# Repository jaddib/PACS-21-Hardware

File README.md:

# PACS-21-Hardware
Here is where we will store our schematics and PCBs
:)

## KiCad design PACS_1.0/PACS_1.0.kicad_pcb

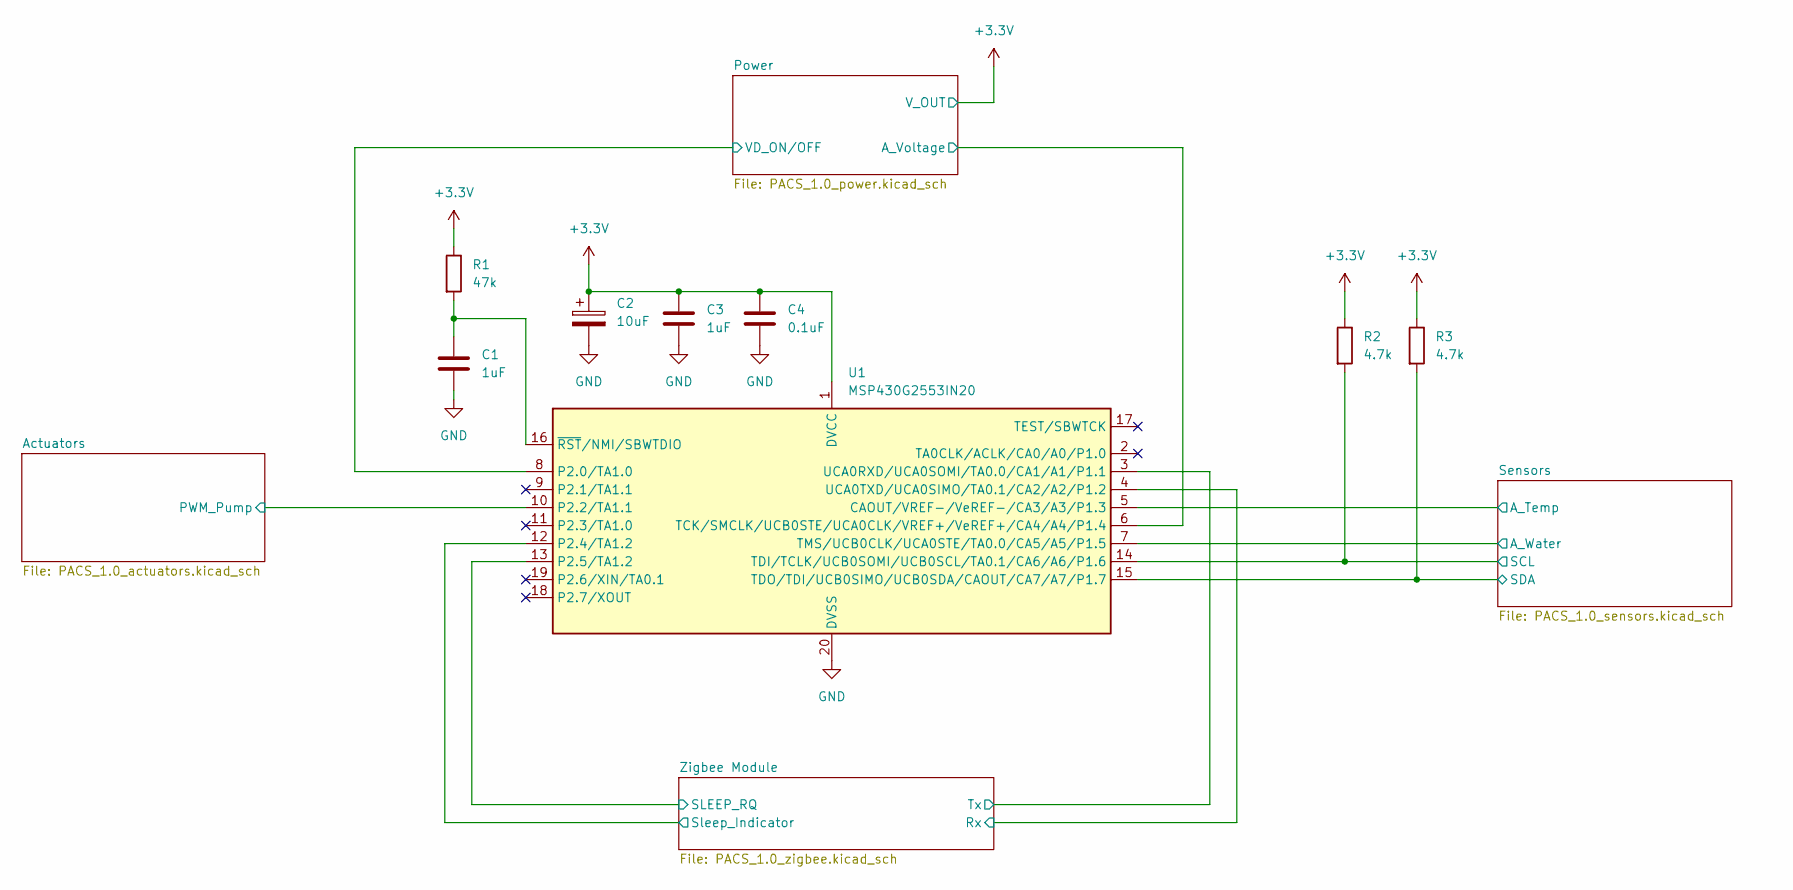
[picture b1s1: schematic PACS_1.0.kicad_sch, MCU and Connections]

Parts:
C1, C3: 1uF; C_0603_1608Metric
C2: 10uF; C_0805_2012Metric
C4: 0.1uF; C_0402_1005Metric
R1: 47k; R_0603_1608Metric
R2, R3: 4.7k; R_0402_1005Metric
U1: MSP430G2553IN20; DIP-20_W7.62mm

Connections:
+3.3V: C2.1, C3.1, C4.1, R1.1, R2.1, R3.1, U1.1 (DVCC); also elsewhere on the board
/Actuators/PWM_Pump: U1.10 (P2.2/TA1.1); also elsewhere on the board
/Power/A_Voltage: U1.6 (TCK/SMCLK/UCB0STE/UCA0CLK/VREF+/VeREF+/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); also elsewhere on the board
/Power/VD_ON/OFF: U1.8 (P2.0/TA1.0); also elsewhere on the board
/Sensors/A_Temp: U1.5 (CAOUT/VREF-/VeREF-/CA3/A3/P1.3); also elsewhere on the board
/Sensors/A_Water: U1.7 (TMS/UCB0CLK/UCA0STE/TA0.0/CA5/A5/P1.5); also elsewhere on the board
/Sensors/SCL: R2.2, U1.14 (TDI/TCLK/UCB0SOMI/UCB0SCL/TA0.1/CA6/A6/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); also elsewhere on the board
/Sensors/SDA: R3.2, U1.15 (TDO/TDI/UCB0SIMO/UCB0SDA/CAOUT/CA7/A7/P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); also elsewhere on the board
/Zigbee Module/Rx: U1.4 (UCA0TXD/UCA0SIMO/TA0.1/CA2/A2/P1.2); also elsewhere on the board
/Zigbee Module/SLEEP_RQ: U1.13 (P2.5/TA1.2); also elsewhere on the board
/Zigbee Module/Sleep_Indicator: U1.12 (P2.4/TA1.2); also elsewhere on the board
/Zigbee Module/Tx: U1.3 (UCA0RXD/UCA0SOMI/TA0.0/CA1/A1/P1.1); also elsewhere on the board
GND: C1.2, C2.2, C3.2, C4.2, U1.20 (DVSS); also elsewhere on the board
unnamed: C1.1, R1.2, U1.16 (~RST/NMI/SBWTDIO)

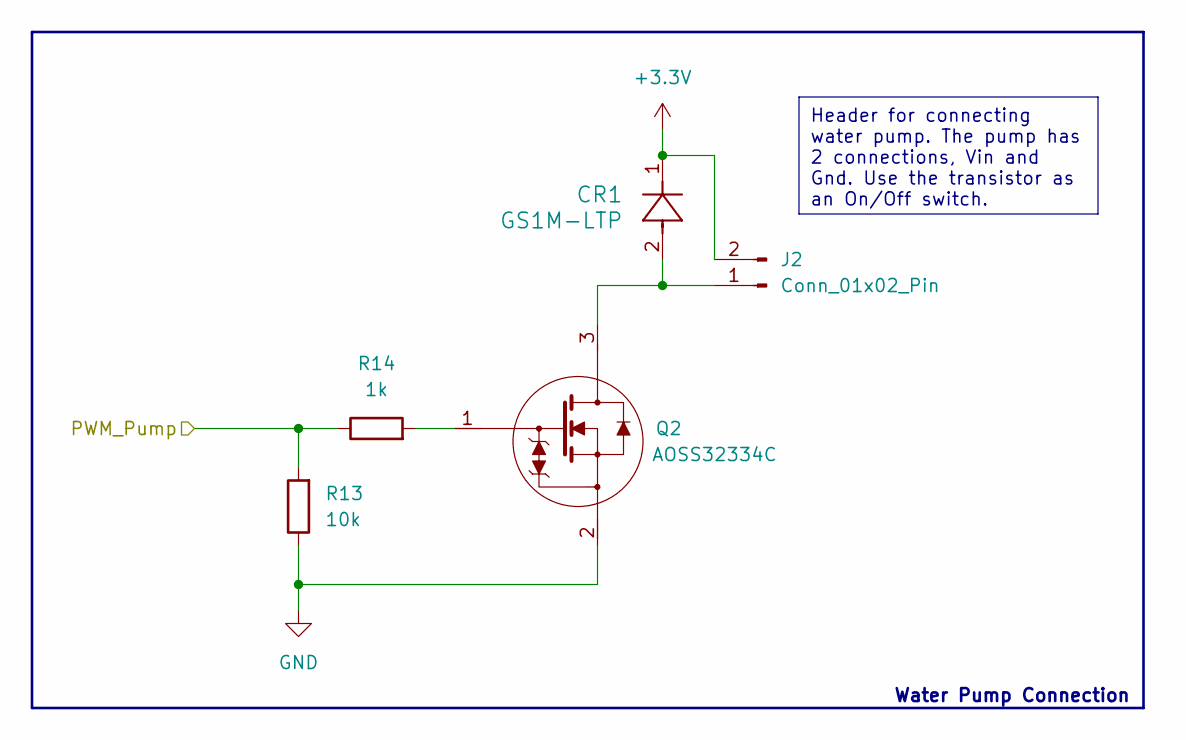
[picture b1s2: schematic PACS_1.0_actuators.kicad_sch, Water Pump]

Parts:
CR1: GS1M-LTP; D_SMA
J2: Conn_01x02_Pin; JST_EH_B2B-EH-A_1x02_P2.50mm_Vertical
Q2: TSOT-23
R13: 10k; R_0402_1005Metric
R14: 1k; R_0402_1005Metric

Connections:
+3.3V: CR1.1, J2.2; also elsewhere on the board
/Actuators/PWM_Pump: R13.2, R14.1; also elsewhere on the board
GND: Q2.2, R13.1; also elsewhere on the board
unnamed: CR1.2, J2.1, Q2.3
unnamed: Q2.1, R14.2

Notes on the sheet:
Header for connecting water pump. The pump has 2 connections, Vin and Gnd. Use the transistor as an On/Off switch.
Water Pump Connection

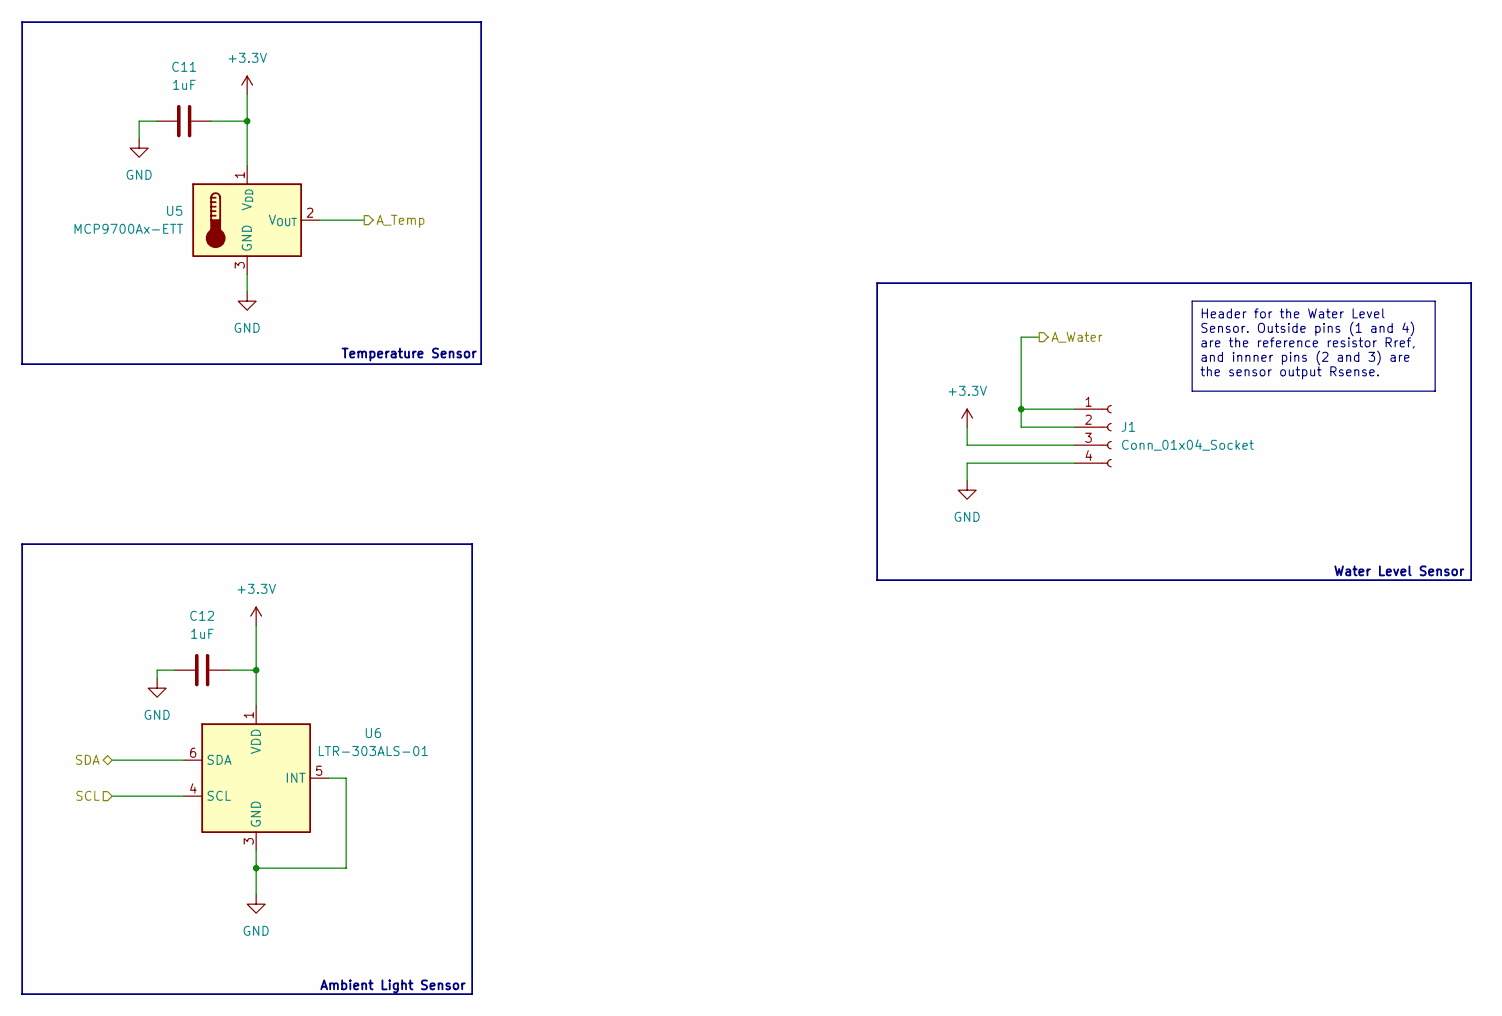
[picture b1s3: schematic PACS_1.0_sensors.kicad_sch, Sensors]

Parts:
C11, C12: 1uF; C_0603_1608Metric
J1: Conn_01x04_Socket; PinSocket_1x04_P2.54mm_Vertical
U5: MCP9700Ax-ETT; SOT-23
U6: LTR-303ALS-01; Lite-On_LTR-303ALS-01

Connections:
+3.3V: C11.2, C12.2, J1.3, U5.1 (V_{DD}), U6.1 (VDD); also elsewhere on the board
/Sensors/A_Temp: U5.2 (V_{OUT}); also elsewhere on the board
/Sensors/A_Water: J1.1, J1.2; also elsewhere on the board
/Sensors/SCL: U6.4 (SCL); also elsewhere on the board
/Sensors/SDA: U6.6 (SDA); also elsewhere on the board
GND: C11.1, C12.1, J1.4, U5.3 (GND), U6.3 (GND), U6.5 (INT); also elsewhere on the board

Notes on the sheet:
Header for the Water Level Sensor. Outside pins (1 and 4) are the reference resistor Rref, and innner pins (2 and 3) are the sensor output Rsense.
Water Level Sensor
Temperature Sensor
Ambient Light Sensor

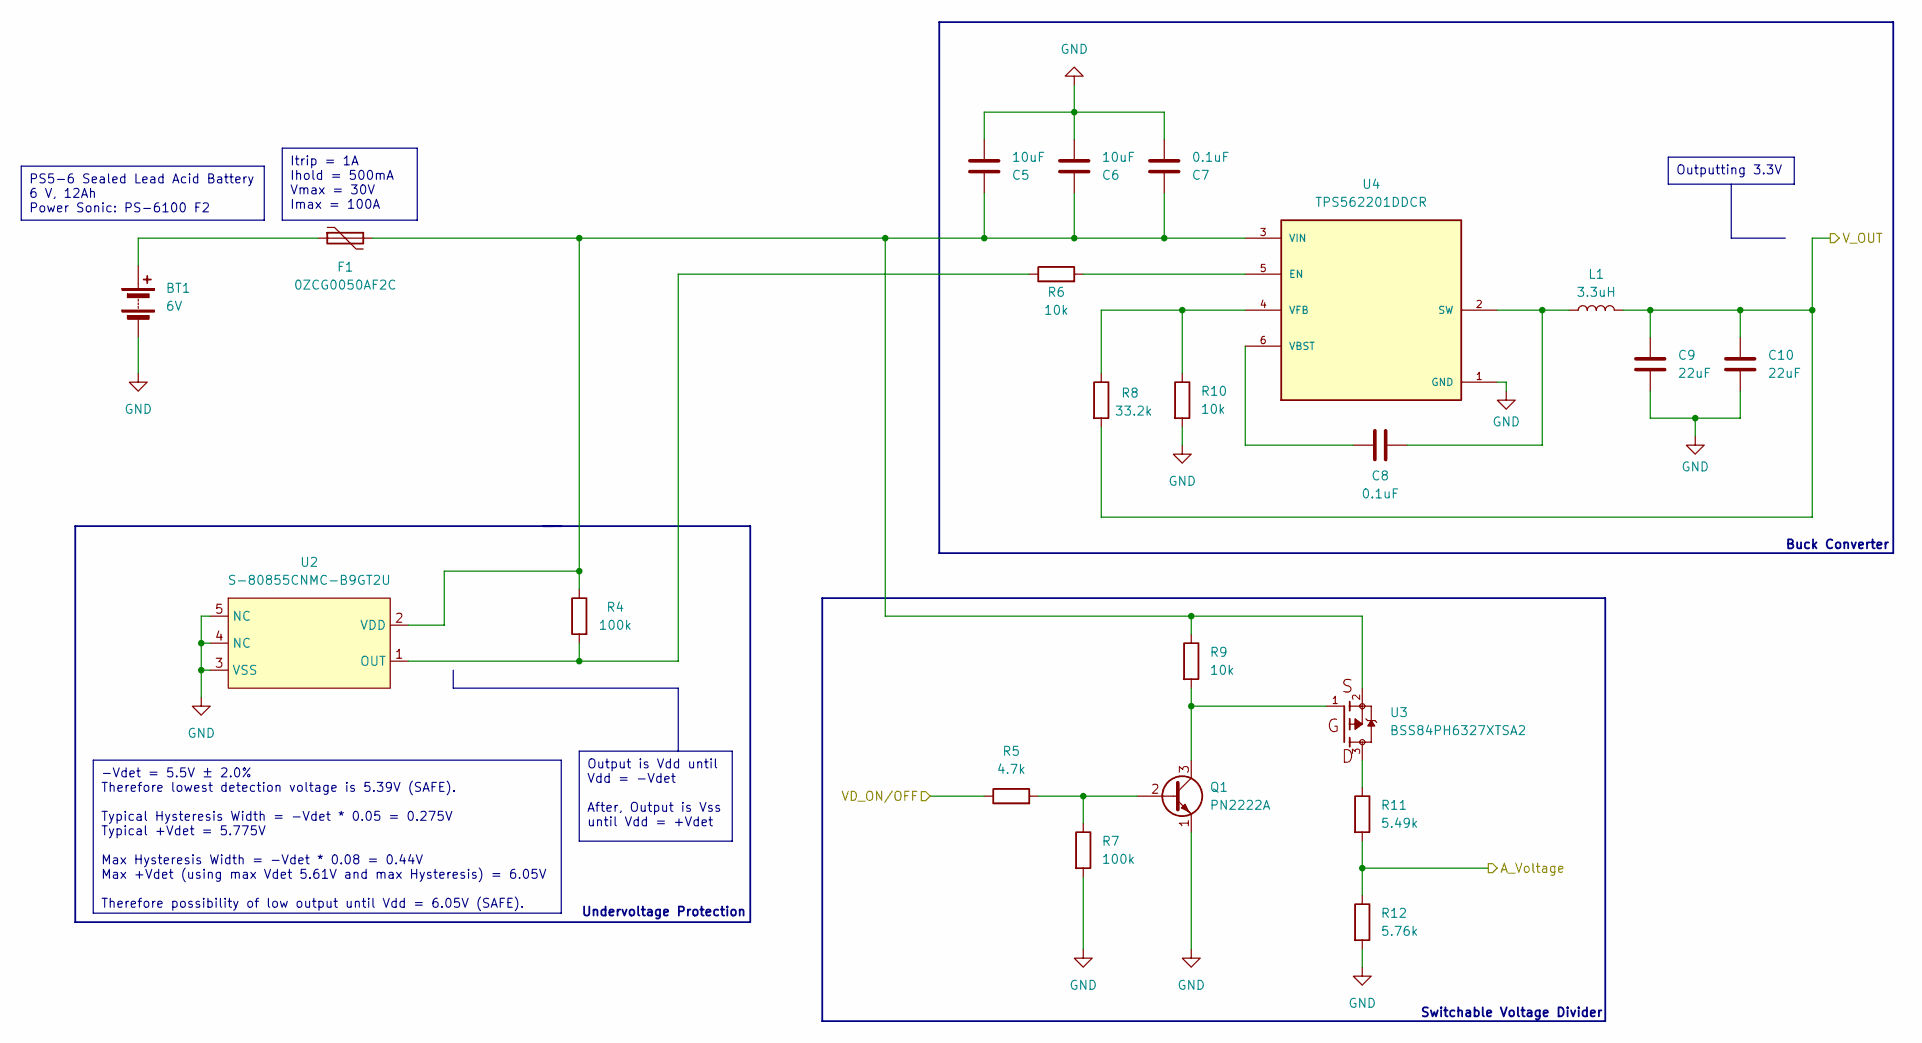
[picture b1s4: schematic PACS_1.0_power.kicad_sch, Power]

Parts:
BT1: 6V; JST_EH_B2B-EH-A_1x02_P2.50mm_Vertical
C5, C6: 10uF; C_0805_2012Metric
C7, C8: 0.1uF; C_0402_1005Metric
C9, C10: 22uF; C_0603_1608Metric
F1: 0ZCG0050AF2C; Fuse_1812_4532Metric
L1: 3.3uH; L_Abracon_ASPI-0630LR
Q1: PN2222A; TO-92_Inline
R4, R7: 100k; R_0402_1005Metric
R5: 4.7k; R_0402_1005Metric
R6, R9, R10: 10k; R_0402_1005Metric
R8: 33.2k; R_0402_1005Metric
R11: 5.49k; R_0603_1608Metric
R12: 5.76k; R_0603_1608Metric
U2: S-80855CNMC-B9GT2U; SOT-23-5
U3: BSS84PH6327XTSA2; TSOT-23
U4: TPS562201DDCR; SOT95P280X110-6N; PARTREV A

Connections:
+3.3V: C9.1, C10.1, L1.2, R8.2; also elsewhere on the board
/Power/A_Voltage: R11.2, R12.1; also elsewhere on the board
/Power/VD_ON/OFF: R5.1; also elsewhere on the board
GND: BT1.2 (-), C5.2, C6.2, C7.2, C9.2, C10.2, Q1.1 (E), R7.2, R10.2, R12.2, U2.3 (VSS), U2.4 (NC), U2.5 (NC), U4.1 (GND); also elsewhere on the board
unnamed: BT1.1 (+), F1.1
unnamed: Q1.2 (B), R5.2, R7.1
unnamed: Q1.3 (C), R9.2, U3.1
unnamed: R11.1, U3.3
unnamed: R4.2, R6.1, U2.1 (OUT)
unnamed: C5.1, C6.1, C7.1, F1.2, R4.1, R9.1, U2.2 (VDD), U3.2, U4.3 (VIN)
unnamed: R6.2, U4.5 (EN)
unnamed: C8.2, L1.1, U4.2 (SW)
unnamed: C8.1, U4.6 (VBST)
unnamed: R8.1, R10.1, U4.4 (VFB)

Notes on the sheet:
Output is Vdd until Vdd = -Vdet After, Output is Vss until Vdd = +Vdet
-Vdet = 5.5V ± 2.0% Therefore lowest detection voltage is 5.39V (SAFE). Typical Hysteresis Width = -Vdet * 0.05 = 0.275V Typical +Vdet = 5.775V Max Hysteresis Width = -Vdet * 0.08 = 0.44V Max +Vdet (using max Vdet 5.61V and max Hysteresis) = 6.05V Therefore possibility of low output until Vdd = 6.0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
Outputting 3.3V
Itrip = 1A Ihold = 500mA Vmax = 30V Imax = 100A
PS5-6 Sealed Lead Acid Battery 6 V, 12Ah Power Sonic: PS-6100 F2
Switchable Voltage Divider
Undervoltage Protection
Buck Converter

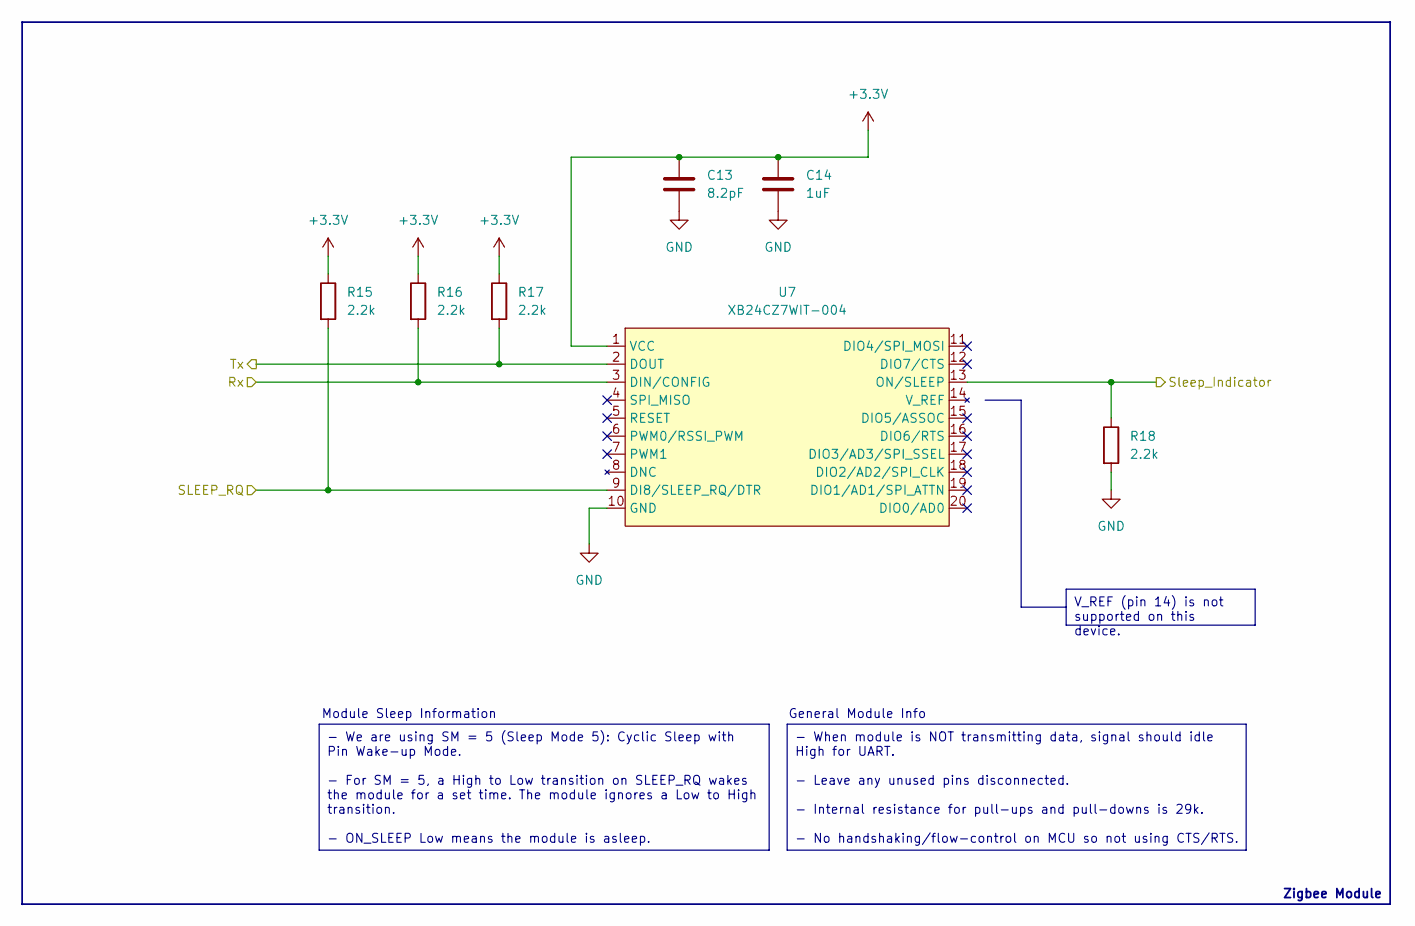
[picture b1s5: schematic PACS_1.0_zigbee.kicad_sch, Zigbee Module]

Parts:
C13: 8.2pF; C_0402_1005Metric
C14: 1uF; C_0603_1608Metric
R15, R16, R17, R18: 2.2k; R_0402_1005Metric
U7: XB24CZ7WIT-004

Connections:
+3.3V: C13.1, C14.1, R15.1, R16.1, R17.1, U7.1 (VCC); also elsewhere on the board
/Zigbee Module/Rx: R16.2, U7.3 (DIN/CONFIG); also elsewhere on the board
/Zigbee Module/SLEEP_RQ: R15.2, U7.9 (DI8/SLEEP_RQ/DTR); also elsewhere on the board
/Zigbee Module/Sleep_Indicator: R18.1, U7.13 (ON/SLEEP); also elsewhere on the board
/Zigbee Module/Tx: R17.2, U7.2 (DOUT); also elsewhere on the board
GND: C13.2, C14.2, R18.2, U7.10 (GND); also elsewhere on the board

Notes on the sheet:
V_REF (pin 14) is not supported on this device.
- We are using SM = 5 (Sleep Mode 5): Cyclic Sleep with Pin Wake-up Mode. - For SM = 5, a High to Low transition on SLEEP_RQ wakes the module for a set time. The module ignores a Low to High transition. - ON_SLEEP Low means the module is asleep.
- When module is NOT transmitting data, signal should idle High for UART. - Leave any unused pins disconnected. - Internal resistance for pull-ups and pull-downs is 29k. - No handshaking/flow-control on MCU so not using CTS/RTS.
Zigbee Module
Module Sleep Information
General Module Info

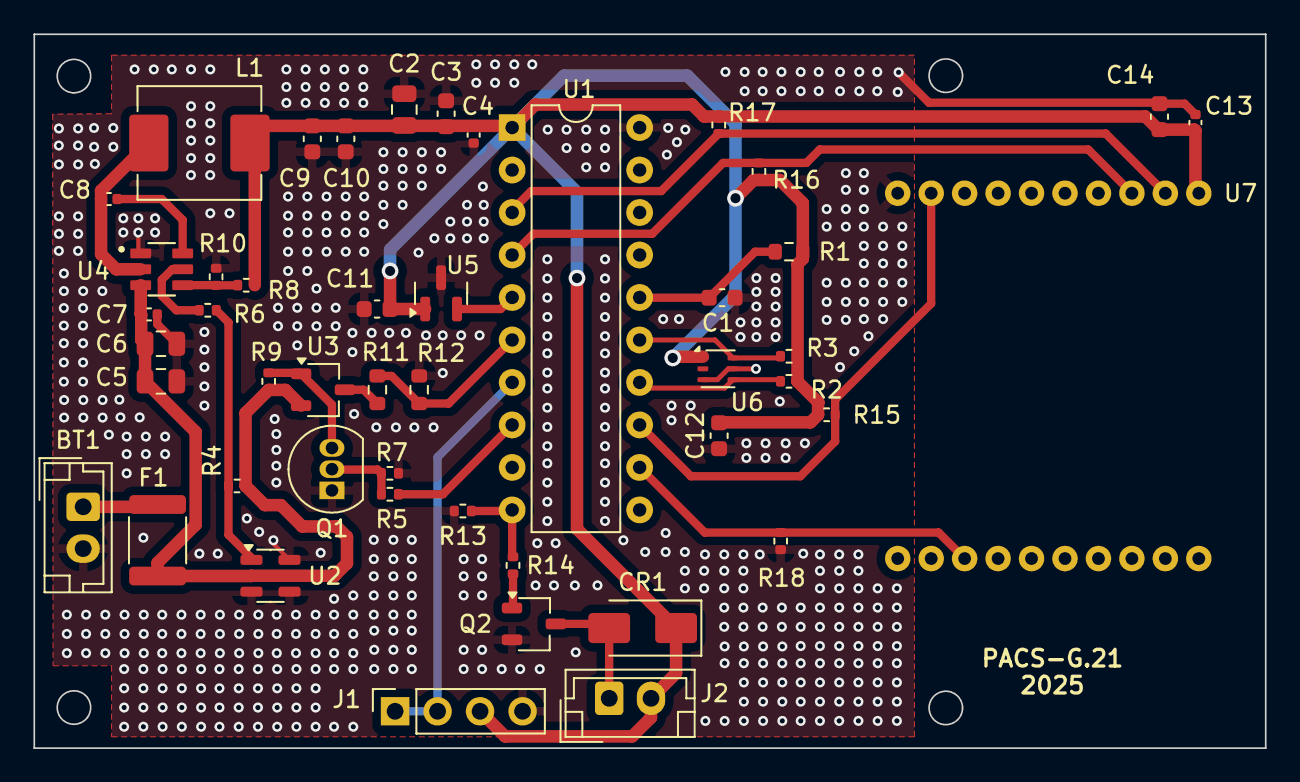
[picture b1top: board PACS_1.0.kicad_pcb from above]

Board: 2 copper layers, 73.6 x 42.7 mm, 47 parts (0 on the bottom side), 26 nets.

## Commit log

2024-11-28 Beginning of the Schematic
    barely anything in here
2024-11-28 Added New Sheets
2024-11-30 Added Bucks, Temp and Light Sensor
2024-11-30 New Changes
    We had the discussion about water pump, INA, LEDS, and battery solution. Not much changes from previous night.
2024-12-01 Added Water level sensor and start of Pump
2024-12-01 Finished water pump, cleaned out empty sheets, added details in 'post its'
2024-12-01 Added LED schematic/PCB
2024-12-03 Finished Zigbee Module
    also fixed some library issues
2024-12-03 Added Undervoltage Protection, removed LED kicad
2024-12-04 Finished 1.0 (NO INA INCLUDED)
    Finished PACS 1.0 sheets, Power sheet needs considerations, no INA yet.
2024-12-06 Changed Battery
2024-12-08 Added skeleton for Voltage Divide
2024-12-09 Finished Voltage Divider
2024-12-09 COMPLETE PACS v1.0
2024-12-09 Changed reference for Components
    C8 to C2 (AS EXAMPLE)
2024-12-09 Changed 5.5k resistor to 5.49k
2024-12-10 Uploaded the PDF of schematic
2024-12-10 Added Boxes and fixed PDF
2025-01-10 Updated footprints for caps and resistors
2025-01-17 added more footprints
2025-01-23 Started the PCB design
    added several footprints, need to find footprint for Xbee, need to add traces for GND and power
2025-01-28 FINISHED PCB DESIGN
    must double check that the dimensions for XBee footprint are correct
2025-01-28 added stitching vias, still need more
    fix library issues
2025-01-30 Added stitching vias
    added names to backside of pcb
2025-02-05 finalized v1.0
2025-02-05 gerber files
2025-02-13 revised PCB with Zoltan housekeeping
    still needs tons of vias for stitching ground planes
2025-02-13 Finished stitching vias
    i think officially complete
2025-02-14 Uploaded PCB to Casptone r1.0
    had to change via sizes to avoid extra costs, set a standard for ground and 3V3
2025-02-16 Removed silkscreen from stitching vias
    created new set of gerber files, revision 2.0
2025-04-10 Add files via upload
    This repository contains Fusion 360 design files for the Plant Automated Care System (PACS). It includes 3D models for the custom enclosure components: the battery compartment, PCB housing, lid for t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
